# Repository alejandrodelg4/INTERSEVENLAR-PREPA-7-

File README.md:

# INTERSEVENLAR-PREPA-7-
Nuestros códigos y diseños:D
Hola, gracias por visitarnos.

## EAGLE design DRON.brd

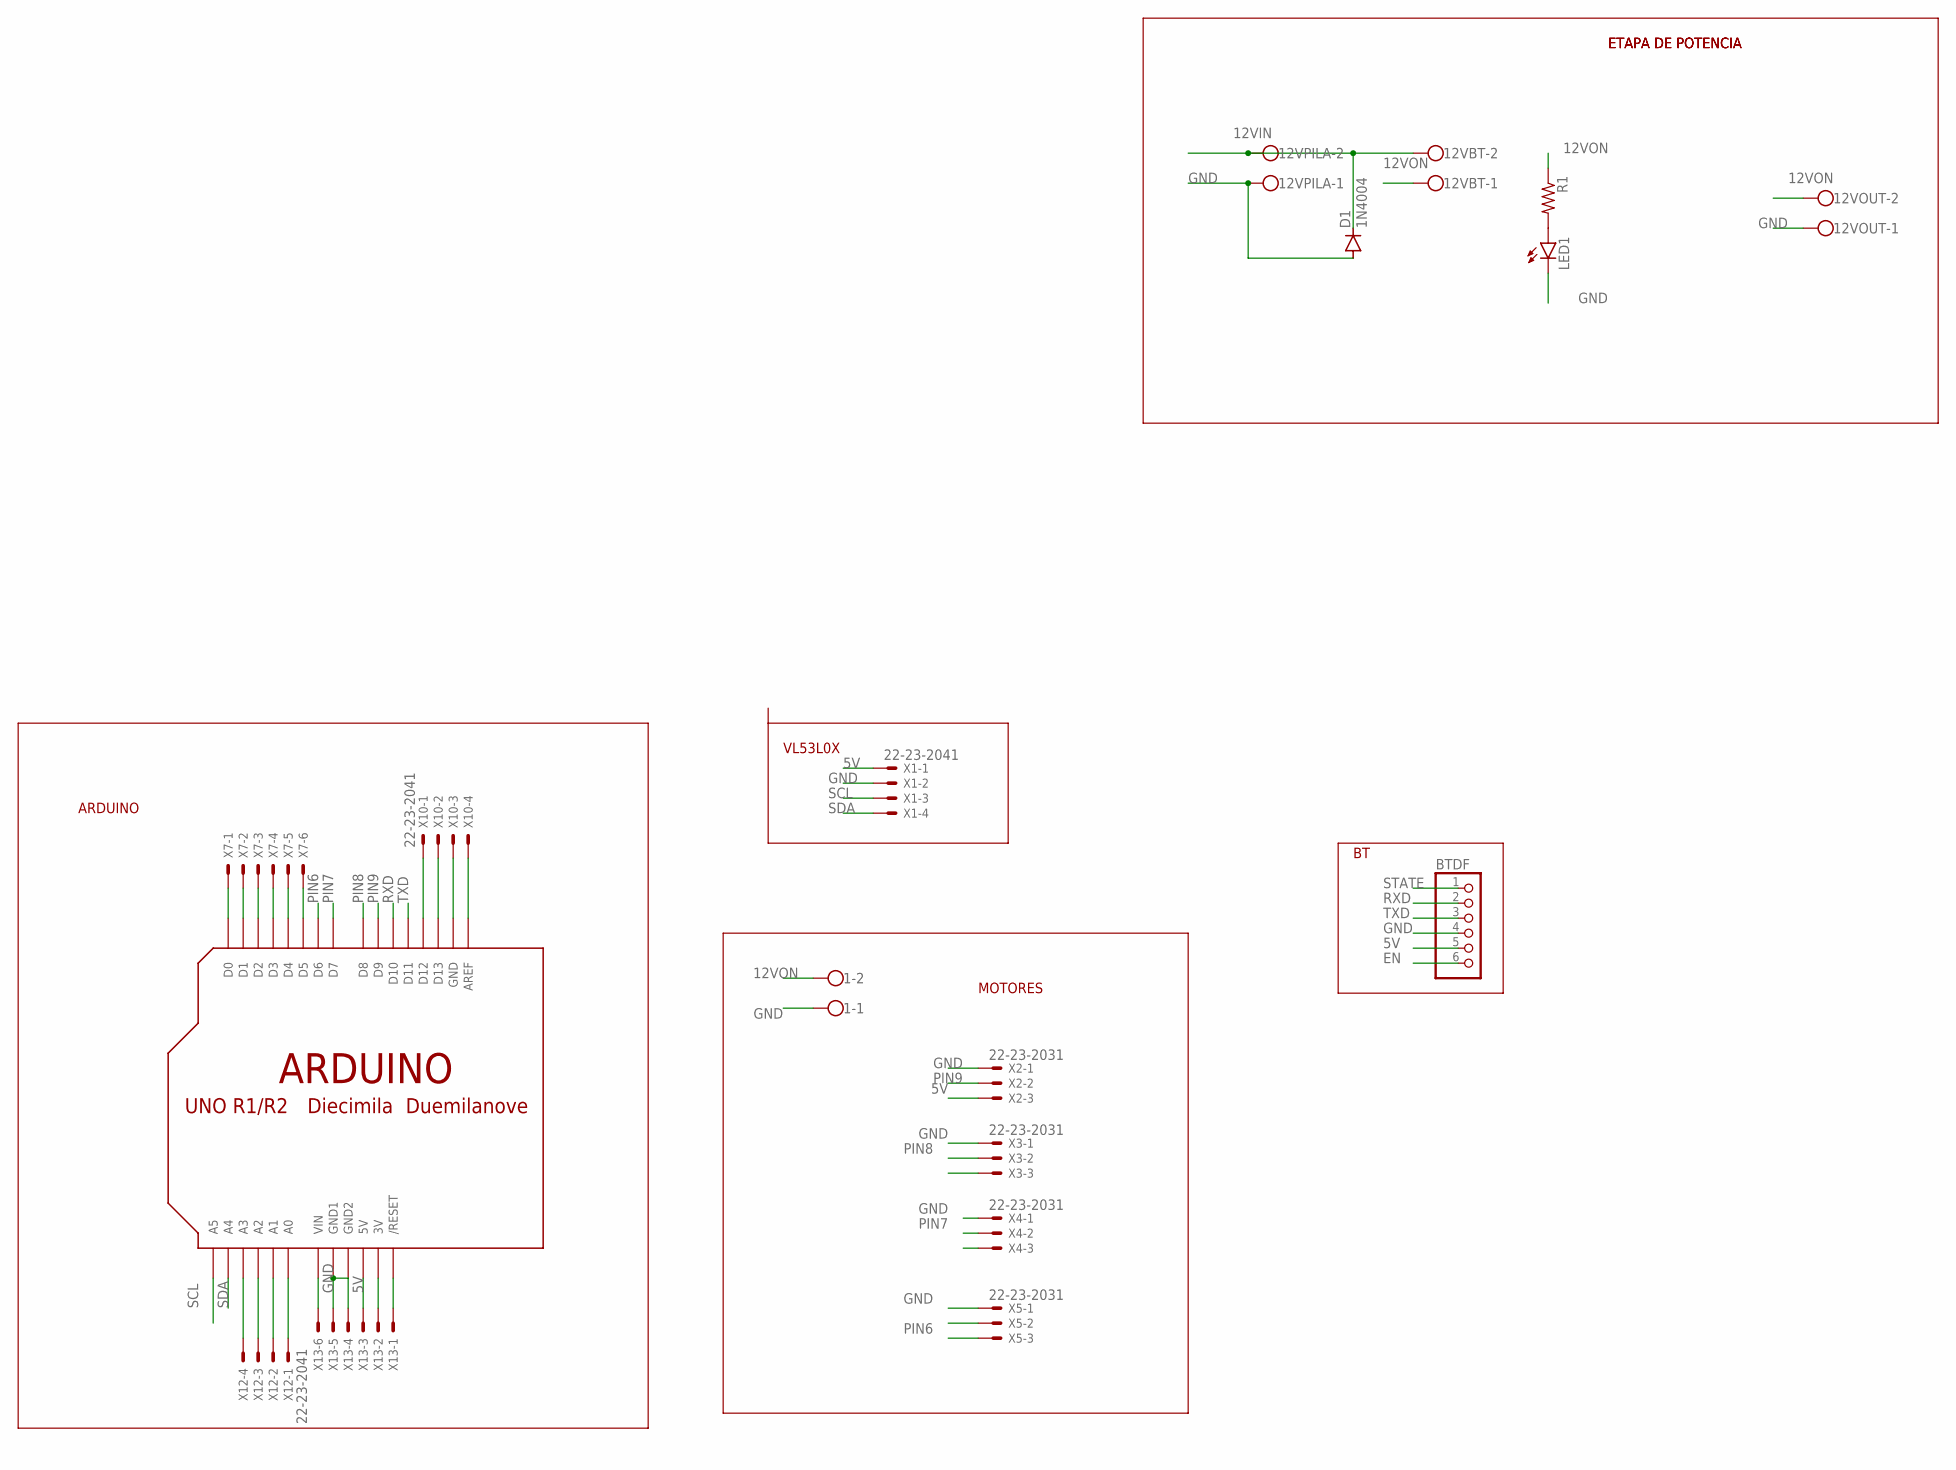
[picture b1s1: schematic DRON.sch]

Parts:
1, 12VBT, 12VOUT, 12VPILA: W237-102
BTDF: PINHD-1X6; 1X06
D1: 1N4004; DO41-10
LED1: LED5MM
R1: R-US_0204/7; 0204/7
U$2: ARDUINO-BPLACE
X1, X10, X12: 22-23-2041
X2, X3, X4, X5: 22-23-2031
X7, X13: 22-23-2061

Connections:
5V: BTDF.5, U$2.5V, X1.1, X2.3, X13.3
12VIN: 12VBT.2, 12VPILA.2, D1.C
12VON: 1.2, 12VBT.1, 12VOUT.2, R1.1
EN: BTDF.6
GND: 1.1, 12VOUT.1, 12VPILA.1, BTDF.4, D1.A, LED1.K (C), U$2.GND1, U$2.GND2, X1.2, X2.1, X3.1, X4.1, X5.1, X13.4, X13.5
unnamed: LED1.A, R1.2
unnamed: U$2.D0, X7.1
unnamed: U$2.D1, X7.2
unnamed: U$2.D2, X7.3
unnamed: U$2.D3, X7.4
unnamed: U$2.D4, X7.5
unnamed: U$2.D5, X7.6
unnamed: U$2.D12, X10.1
unnamed: U$2.D13, X10.2
unnamed: U$2.GND, X10.3
unnamed: U$2.AREF, X10.4
unnamed: U$2.VIN, X13.6
unnamed: U$2.3V, X13.2
unnamed: U$2.RESET (/RESET), X13.1
unnamed: U$2.A3, X12.4
unnamed: U$2.A2, X12.3
unnamed: U$2.A1, X12.2
unnamed: U$2.A0, X12.1
PIN6: U$2.D6, X5.2
PIN7: U$2.D7, X4.2
PIN8: U$2.D8, X3.2
PIN9: U$2.D9, X2.2
RXD: BTDF.2, U$2.D10
SCL: U$2.A5, X1.3
SDA: U$2.A4, X1.4
STATE: BTDF.1
TXD: BTDF.3, U$2.D11

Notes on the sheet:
ETAPA DE POTENCIA
ARDUINO
MOTORES
VL53L0X

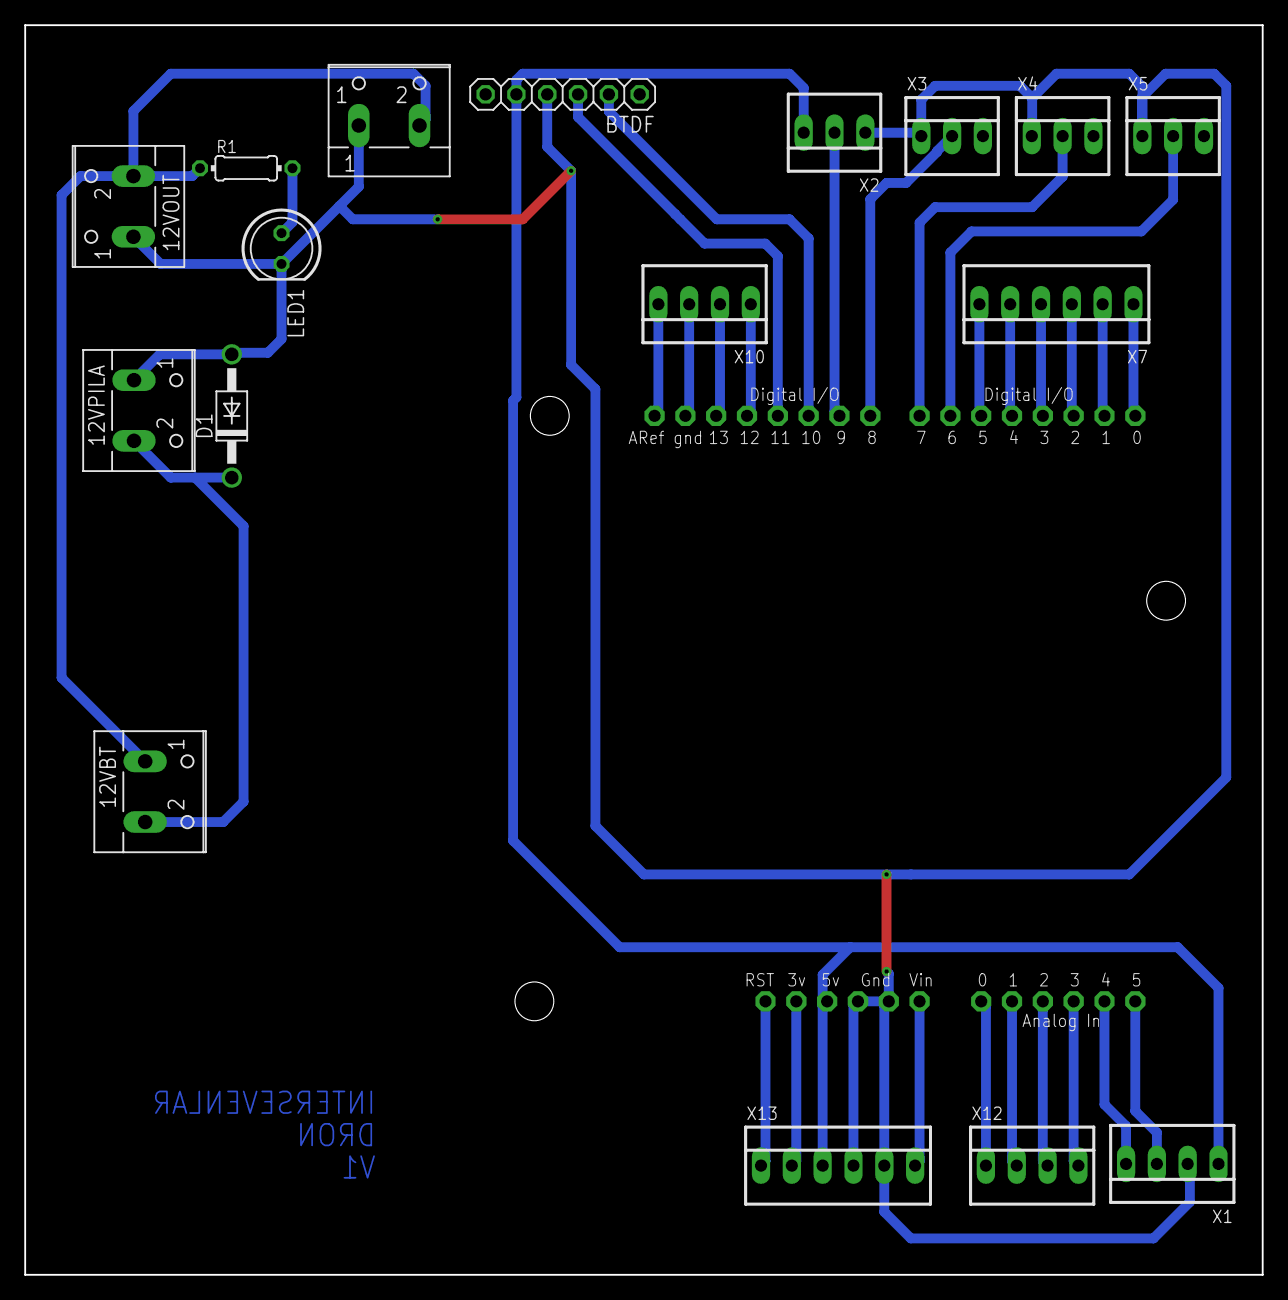
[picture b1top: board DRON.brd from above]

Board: 2 copper layers, 102.0 x 103.0 mm, 18 parts (0 on the bottom side), 30 nets.

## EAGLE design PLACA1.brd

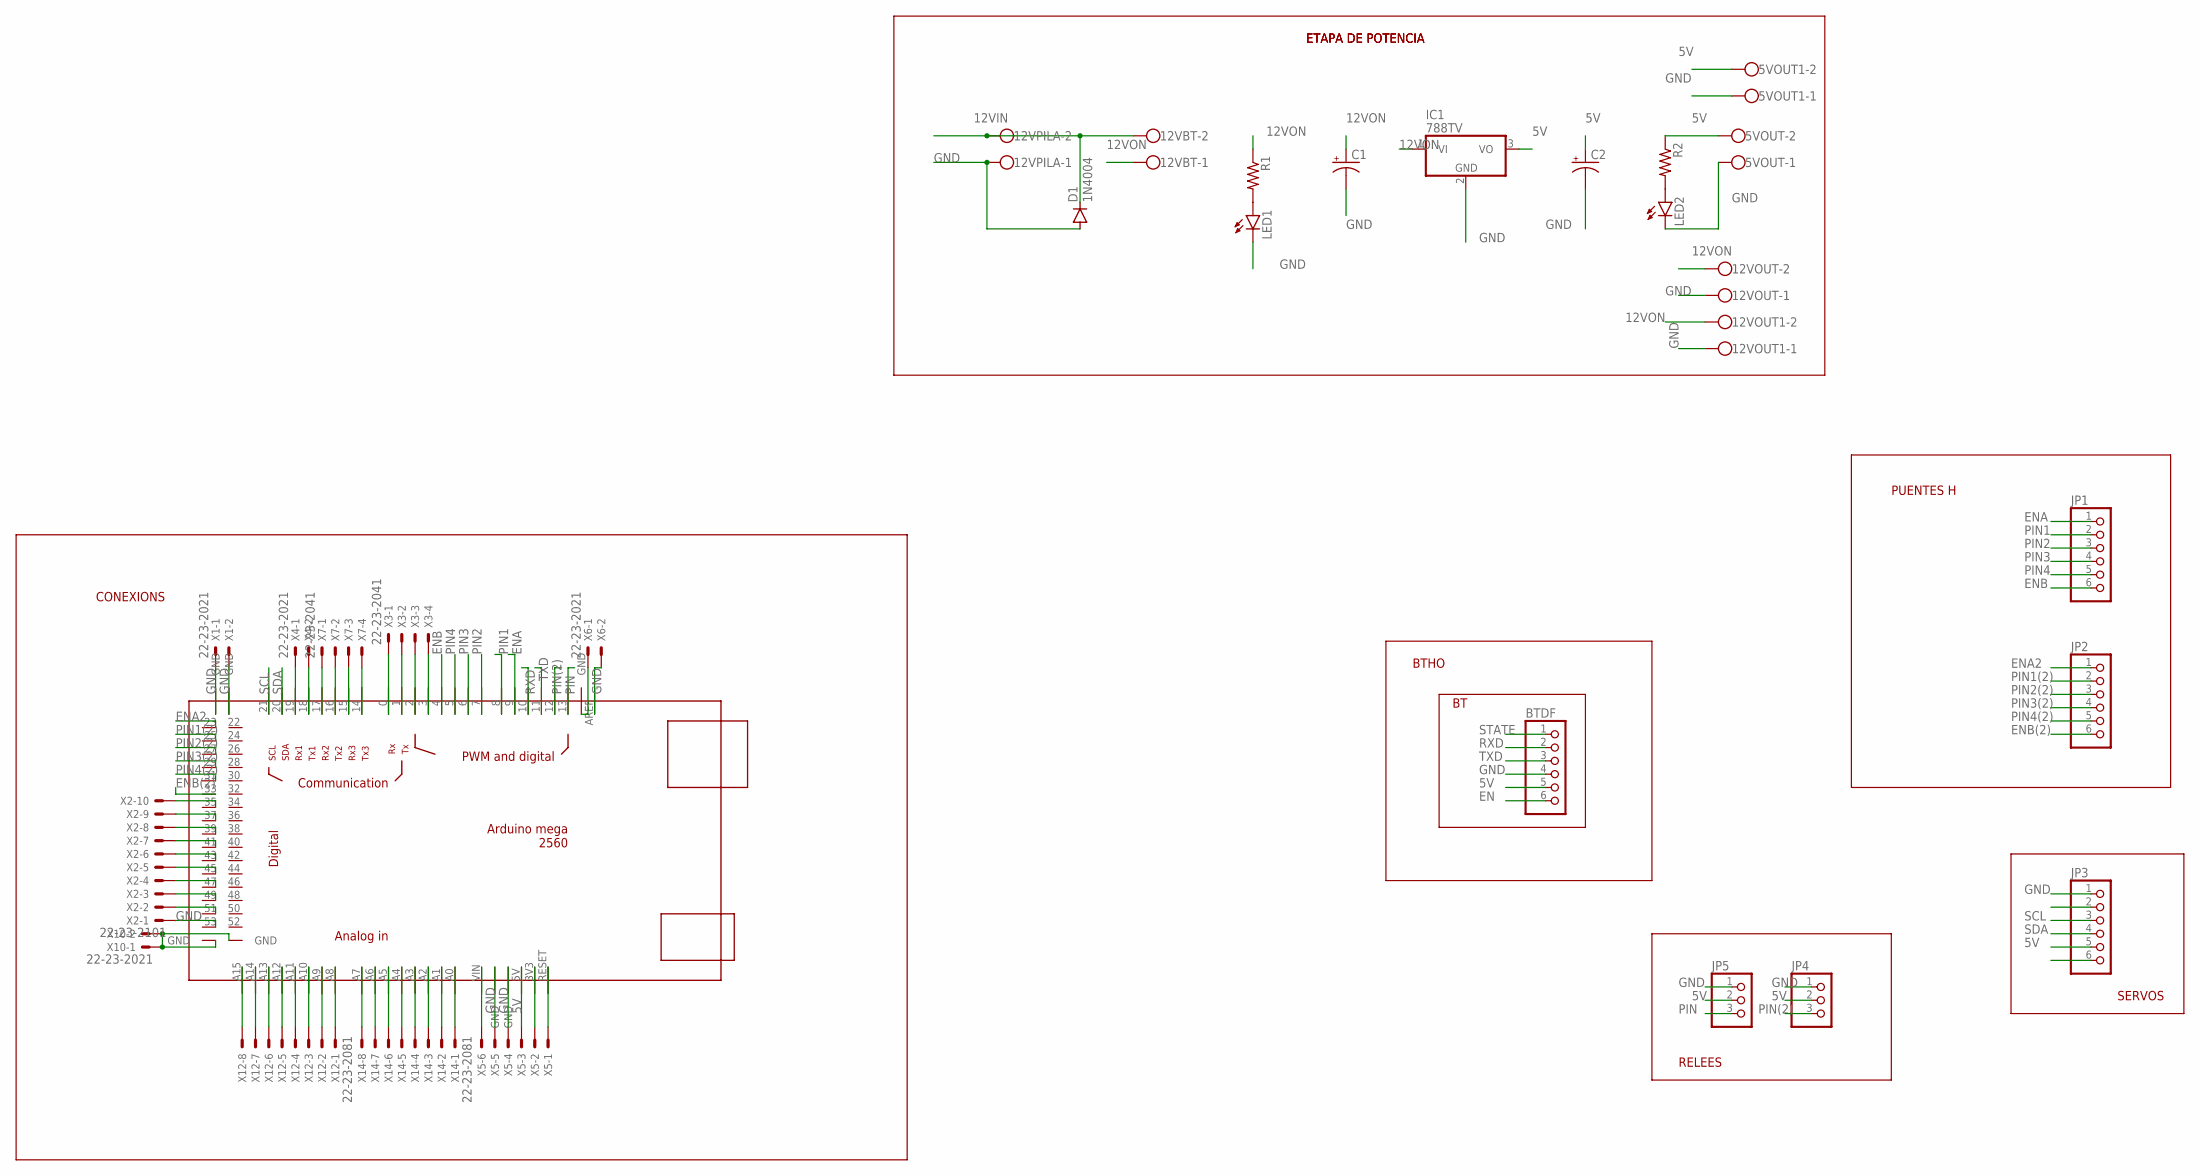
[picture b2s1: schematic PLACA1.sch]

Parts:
5VOUT, 5VOUT1, 12VBT, 12VOUT, 12VOUT1, 12VPILA: W237-102
BTDF: PINHD-1X6; 1X06
C1, C2: CPOL-USE1.8-4; E1,8-4
D1: 1N4004; DO41-10
IC1: 788TV; TO220V
JP1, JP2, JP3: PINHD-1X6; 1X06
JP4, JP5: PINHD-1X3; 1X03
LED1, LED2: LED5MM
R1, R2: R-US_0204/7; 0204/7
U$1: MEGA_DEVICE; MEGAOUTLINE
X1, X4, X6, X10: 22-23-2021
X2: 22-23-2101
X3, X7: 22-23-2041
X5: 22-23-2061
X12, X14: 22-23-2081

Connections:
5V: 5VOUT.2, 5VOUT1.2, BTDF.5, C2.+, IC1.3 (VO), JP3.5, JP4.2, JP5.2, R2.1, U$1.5V, X5.3
12VIN: 12VBT.2, 12VPILA.2, D1.C
12VON: 12VBT.1, 12VOUT.2, 12VOUT1.2, C1.+, IC1.1 (VI), R1.1
EN: BTDF.6
ENA: JP1.1, U$1.9
ENA2: JP2.1, U$1.23
ENB: JP1.6, U$1.4
ENB(2): JP2.6, U$1.33
GND: 5VOUT.1, 5VOUT1.1, 12VOUT.1, 12VOUT1.1, 12VPILA.1, BTDF.4, C1.-, C2.-, D1.A, IC1.2 (GND), JP3.1, JP4.1, JP5.1, LED1.K (C), LED2.K (C), U$1.GND@1 (GND), U$1.GND@2 (GND), U$1.GND@3 (GND), U$1.GND@4 (GND), U$1.GND@5 (GND), U$1.GND@6 (GND), U$1.GND@7 (GND), X1.1, X1.2, X5.4, X5.5, X6.1, X10.1, X10.2
unnamed: LED1.A, R1.2
unnamed: U$1.35, X2.10
unnamed: U$1.37, X2.9
unnamed: U$1.17, X7.1
unnamed: LED2.A, R2.2
unnamed: U$1.16, X7.2
unnamed: U$1.15, X7.3
unnamed: U$1.14, X7.4
unnamed: U$1.0, X3.1
unnamed: U$1.1, X3.2
unnamed: U$1.2, X3.3
unnamed: U$1.3, X3.4
unnamed: U$1.19, X4.1
unnamed: U$1.18, X4.2
unnamed: U$1.39, X2.8
unnamed: U$1.41, X2.7
unnamed: U$1.43, X2.6
unnamed: U$1.45, X2.5
unnamed: U$1.AREF, X6.2
unnamed: U$1.A15, X12.8
unnamed: U$1.A14, X12.7
unnamed: U$1.A13, X12.6
unnamed: U$1.A12, X12.5
unnamed: U$1.A11, X12.4
unnamed: U$1.A10, X12.3
unnamed: U$1.A9, X12.2
unnamed: U$1.A8, X12.1
unnamed: U$1.A7, X14.8
unnamed: U$1.A6, X14.7
unnamed: U$1.A5, X14.6
unnamed: U$1.A4, X14.5
unnamed: U$1.A3, X14.4
unnamed: U$1.A2, X14.3
unnamed: U$1.A1, X14.2
unnamed: U$1.A0, X14.1
unnamed: U$1.VIN, X5.6
unnamed: U$1.47, X2.4
unnamed: U$1.49, X2.3
unnamed: U$1.51, X2.2
unnamed: U$1.3V3, X5.2
unnamed: U$1.RESET, X5.1
unnamed: U$1.53, X2.1
PIN: JP5.3, U$1.13
PIN1: JP1.2, U$1.8
PIN1(2): JP2.2, U$1.25
PIN2: JP1.3, U$1.7
PIN2(2): JP2.3, U$1.27
PIN3: JP1.4, U$1.6
PIN3(2): JP2.4, U$1.29
PIN4: JP1.5, U$1.5
PIN4(2): JP2.5, U$1.31
PIN(2): JP4.3, U$1.12
RXD: BTDF.2, U$1.10
SCL: JP3.3, U$1.21
SDA: JP3.4, U$1.20
STATE: BTDF.1
TXD: BTDF.3, U$1.11

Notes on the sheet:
ETAPA DE POTENCIA
CONEXIONS
BTHO
PUENTES H
SERVOS
RELEES

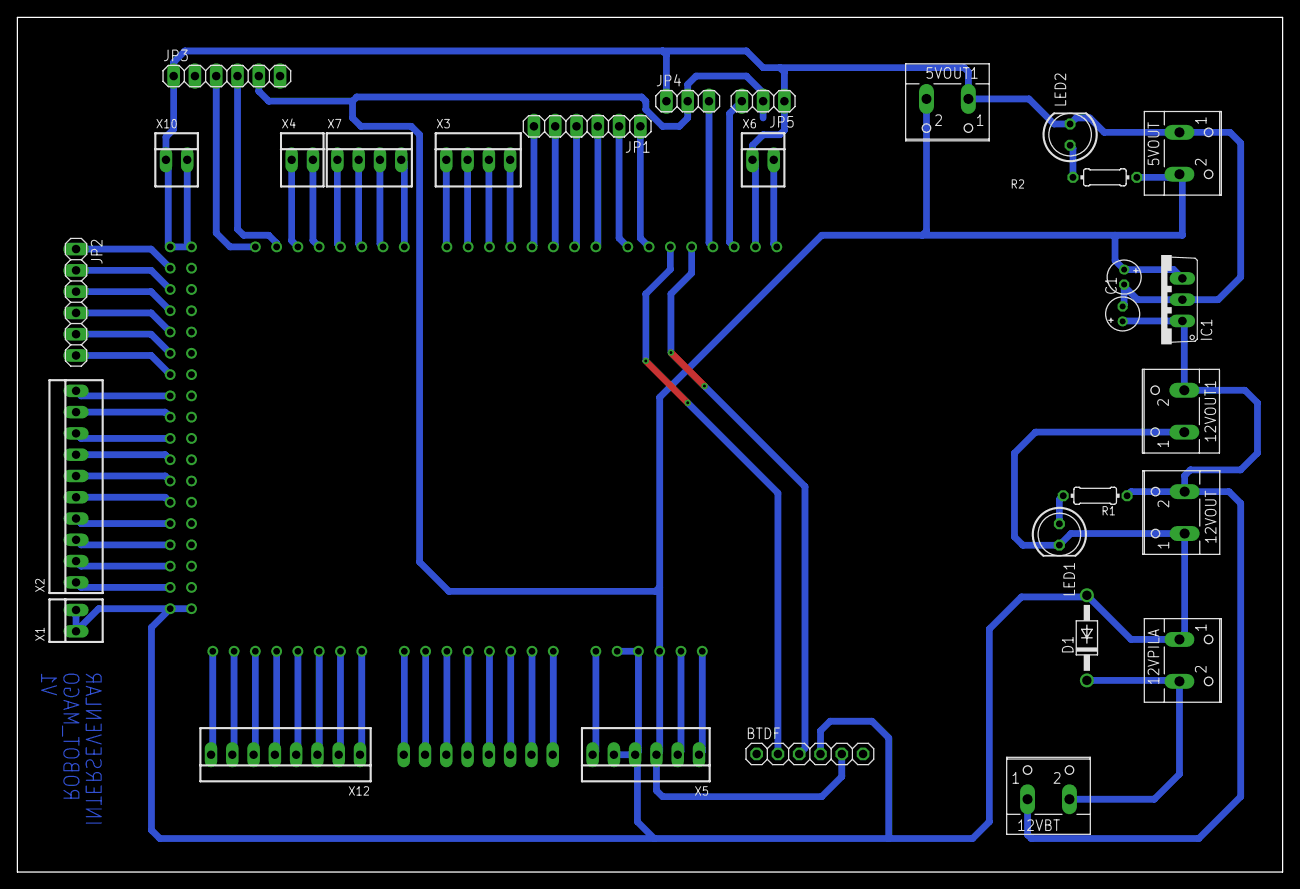
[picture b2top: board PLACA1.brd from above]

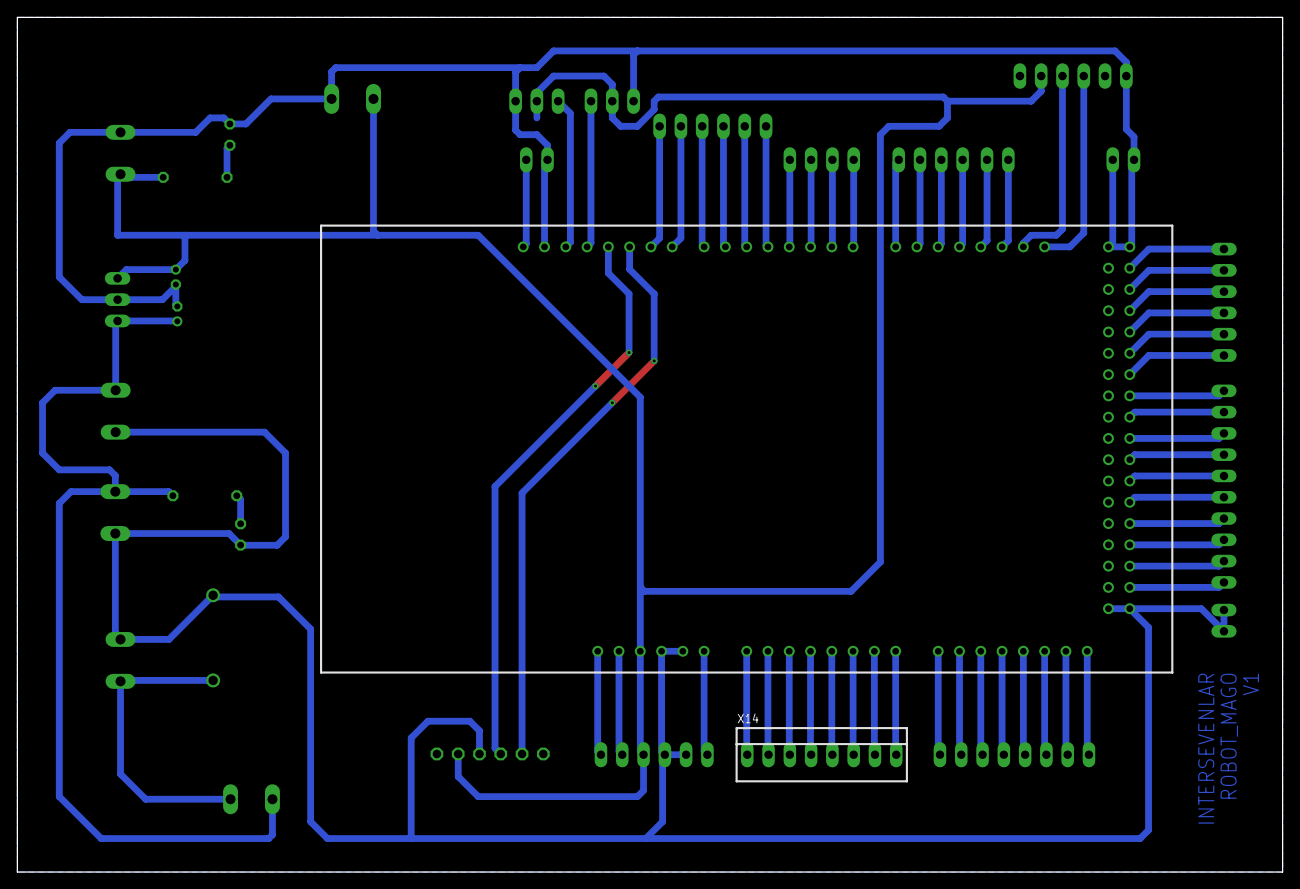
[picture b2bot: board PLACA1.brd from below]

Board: 2 copper layers, 151.0 x 102.0 mm, 31 parts (2 on the bottom side), 64 nets.

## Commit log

2023-11-08 Create CODIGO DE VOZ
2023-11-08 Create PRUEBA DE MOVIMIENTOS DE BRAZOS
2023-11-08 Rename PRUEBA DE MOVIMIENTOS DE BRAZOS to PRUEBA DE MOVIMIENTOS DE BRAZOS POR PUERTO SERIAL.ino
2023-11-08 Create PRUEBA DE MOTORES
2023-11-08 Rename PRUEBA DE MOTORES to PRUEBA DE MOTORES.ino
2023-11-08 DISEÑOS DE PCB'S
    Aquí podrás encontrar los diseños de nuestras PBC's realizadas por nosotros en EAGLE
2023-11-08 CODIGOS Y DISEÑOS (PCB'S E IMPRESIONES 3D)
2023-11-08 Rename PLACA1.sch to PLACA_MAGO.sch
2023-11-08 Rename PLACA1.brd to PLACA1_MAGO.brd
